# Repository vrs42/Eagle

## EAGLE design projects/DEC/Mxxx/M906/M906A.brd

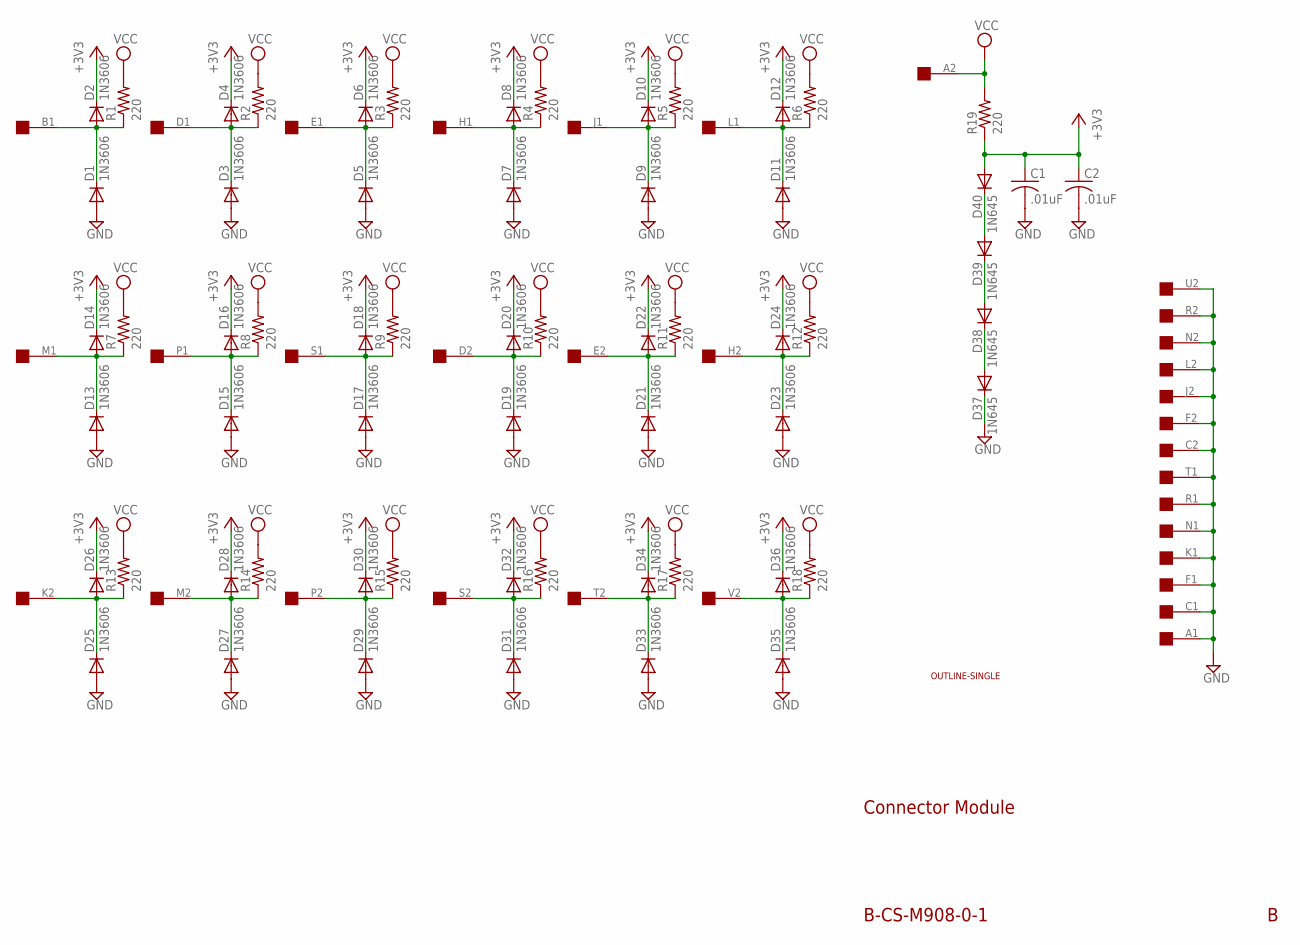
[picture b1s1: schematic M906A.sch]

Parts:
C1, C2: .01uF; C050-025X075
D1, D2, D3, D4, D5, D6, D7, D8, D9, D10, D11, D12, D13, D14, D15, D16, D17, D18, D19, D20, D21, D22, D23, D24, D25, D26, D27, D28, D29, D30, D31, D32, D33, D34, D35, D36: 1N3606; DO35-10
D37, D38, D39, D40: 1N645; DO35-10
R1, R2, R3, R4, R5, R6, R7, R8, R9, R10, R11, R12, R13, R14, R15, R16, R17, R18, R19: 220; 0207/10
U$1: SINGLE; EDGE-CON2
U$2: OUTLINE-SINGLE; SINGLE

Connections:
+3V3: C1.1, C2.1, D2.C, D4.C, D6.C, D8.C, D10.C, D12.C, D14.C, D16.C, D18.C, D20.C, D22.C, D24.C, D26.C, D28.C, D30.C, D32.C, D34.C, D36.C, D40.A, R19.1
GND: C1.2, C2.2, D1.A, D3.A, D5.A, D7.A, D9.A, D11.A, D13.A, D15.A, D17.A, D19.A, D21.A, D23.A, D25.A, D27.A, D29.A, D31.A, D33.A, D35.A, D37.C, U$1.A1, U$1.C1, U$1.C2, U$1.F1, U$1.F2, U$1.J2, U$1.K1, U$1.L2, U$1.N1, U$1.N2, U$1.R1, U$1.R2, U$1.T1, U$1.U2
unnamed: D1.C, D2.A, R1.1, U$1.B1
unnamed: D37.A, D38.C
unnamed: D38.A, D39.C
unnamed: D3.C, D4.A, R2.1, U$1.D1
unnamed: D39.A, D40.C
unnamed: D5.C, D6.A, R3.1, U$1.E1
unnamed: D7.C, D8.A, R4.1, U$1.H1
unnamed: D9.C, D10.A, R5.1, U$1.J1
unnamed: D11.C, D12.A, R6.1, U$1.L1
unnamed: D13.C, D14.A, R7.1, U$1.M1
unnamed: D15.C, D16.A, R8.1, U$1.P1
unnamed: D17.C, D18.A, R9.1, U$1.S1
unnamed: D19.C, D20.A, R10.1, U$1.D2
unnamed: D21.C, D22.A, R11.1, U$1.E2
unnamed: D23.C, D24.A, R12.1, U$1.H2
unnamed: D25.C, D26.A, R13.1, U$1.K2
unnamed: D27.C, D28.A, R14.1, U$1.M2
unnamed: D29.C, D30.A, R15.1, U$1.P2
unnamed: D31.C, D32.A, R16.1, U$1.S2
unnamed: D33.C, D34.A, R17.1, U$1.T2
unnamed: D35.C, D36.A, R18.1, U$1.V2
VCC: R1.2, R2.2, R3.2, R4.2, R5.2, R6.2, R7.2, R8.2, R9.2, R10.2, R11.2, R12.2, R13.2, R14.2, R15.2, R16.2, R17.2, R18.2, R19.2, U$1.A2

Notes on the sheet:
Connector Module
B-CS-M908-0-1

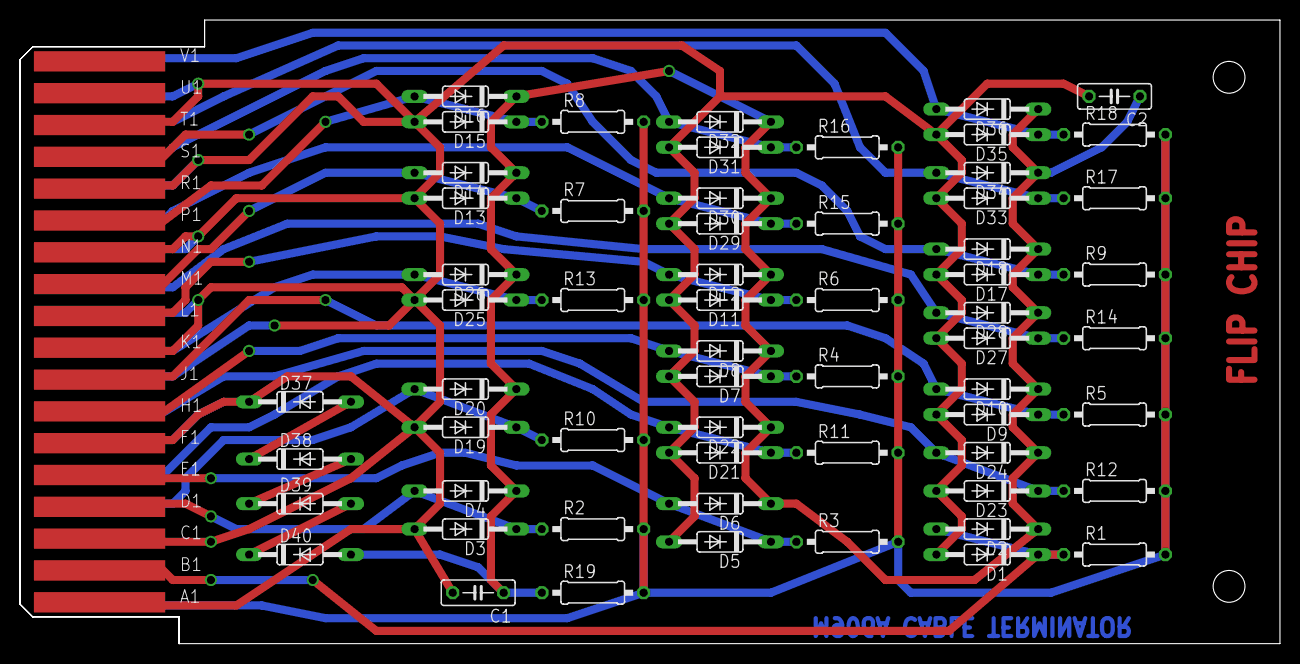
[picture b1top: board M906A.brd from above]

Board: 2 copper layers, 125.7 x 62.2 mm, 64 parts (0 on the bottom side), 24 nets.

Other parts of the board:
U$3: FLIPCHIP

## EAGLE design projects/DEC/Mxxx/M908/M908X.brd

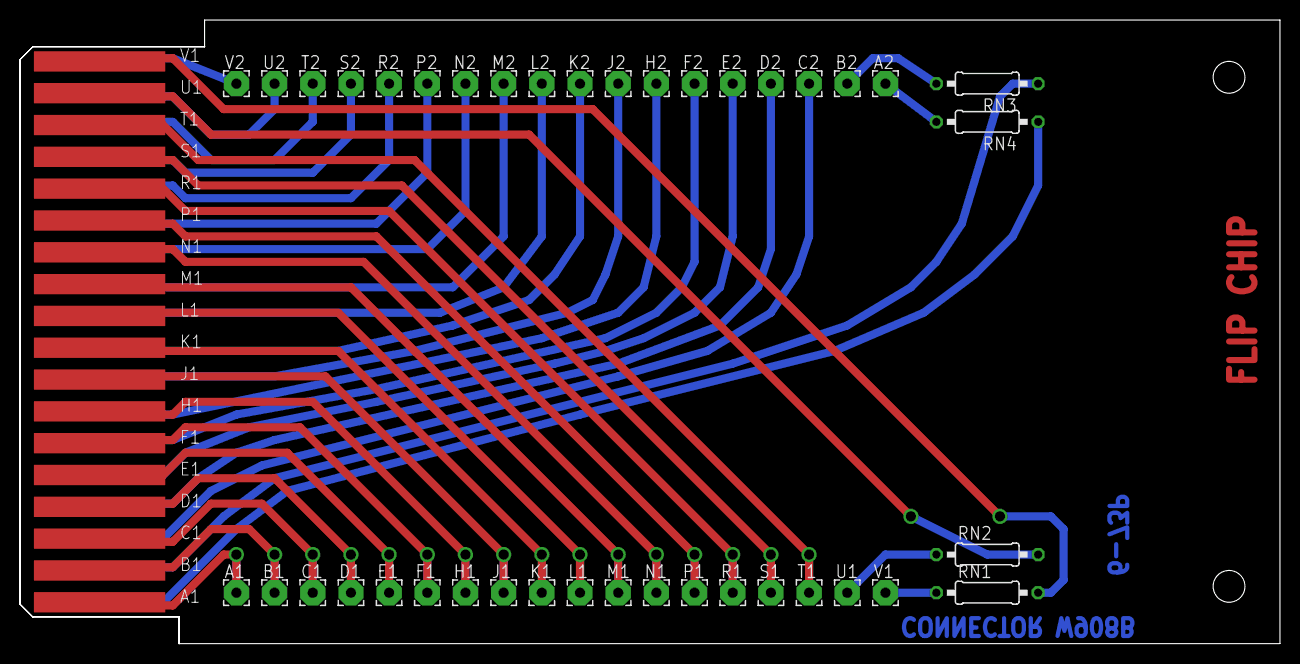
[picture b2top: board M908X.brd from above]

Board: 2 copper layers, 125.7 x 62.2 mm, 43 parts (0 on the bottom side), 40 nets.

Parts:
A1, A2: 2,54/1,0
B1, B2: 2,54/1,0
C1, C2: 2,54/1,0
D1, D2: 2,54/1,0
E1, E2: 2,54/1,0
F1, F2: 2,54/1,0
H1, H2: 2,54/1,0
J1, J2: 2,54/1,0
K1, K2: 2,54/1,0
L1, L2: 2,54/1,0
M1, M2: 2,54/1,0
N1, N2: 2,54/1,0
P1, P2: 2,54/1,0
R1, R2: 2,54/1,0
RN1, RN2, RN3, RN4: 10; 0207/10
S1, S2: 2,54/1,0
T1, T2: 2,54/1,0
U1, U2: 2,54/1,0
U$1: EDGE-CON2
U$2: OUTLINE-SINGLE; SINGLE
U$3: FLIPCHIP
V1, V2: 2,54/1,0

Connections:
unnamed: D1.1, U$1.D1
unnamed: E1.1, U$1.E1
unnamed: F1.1, U$1.F1
unnamed: H1.1, U$1.H1
unnamed: J1.1, U$1.J1
unnamed: K1.1, U$1.K1
unnamed: L1.1, U$1.L1
unnamed: M1.1, U$1.M1
unnamed: N1.1, U$1.N1
unnamed: P1.1, U$1.P1
unnamed: R1.1, U$1.R1
unnamed: S1.1, U$1.S1
unnamed: T1.1, U$1.T1
unnamed: RN2.2, U$1.U1
unnamed: RN1.2, U$1.V1
unnamed: A2.1, RN4.2
unnamed: B2.1, RN3.2
unnamed: C2.1, U$1.C2
unnamed: D2.1, U$1.D2
unnamed: E2.1, U$1.E2
unnamed: F2.1, U$1.F2
unnamed: H2.1, U$1.H2
unnamed: J2.1, U$1.J2
unnamed: K2.1, U$1.K2
unnamed: L2.1, U$1.L2
unnamed: M2.1, U$1.M2
unnamed: N2.1, U$1.N2
unnamed: P2.1, U$1.P2
unnamed: R2.1, U$1.R2
unnamed: S2.1, U$1.S2
unnamed: T2.1, U$1.T2
unnamed: U2.1, U$1.U2
unnamed: U$1.V2, V2.1
unnamed: RN1.1, V1.1
unnamed: RN2.1, U1.1
unnamed: RN3.1, U$1.B2
unnamed: RN4.1, U$1.A2
unnamed: A1.1, U$1.A1
unnamed: B1.1, U$1.B1
unnamed: C1.1, U$1.C1

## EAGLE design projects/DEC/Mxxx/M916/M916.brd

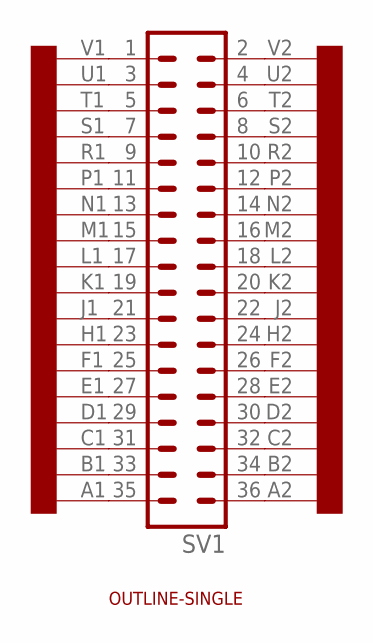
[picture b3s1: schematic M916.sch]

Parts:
SV1: MA18-2
U$1: EDGE-2CONNECTOR; EDGE-CON2
U$2: OUTLINE-SINGLE; SINGLE

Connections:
unnamed: SV1.1, U$1.V1
unnamed: SV1.3, U$1.U1
unnamed: SV1.5, U$1.T1
unnamed: SV1.7, U$1.S1
unnamed: SV1.9, U$1.R1
unnamed: SV1.11, U$1.P1
unnamed: SV1.13, U$1.N1
unnamed: SV1.15, U$1.M1
unnamed: SV1.17, U$1.L1
unnamed: SV1.19, U$1.K1
unnamed: SV1.21, U$1.J1
unnamed: SV1.23, U$1.H1
unnamed: SV1.25, U$1.F1
unnamed: SV1.27, U$1.E1
unnamed: SV1.29, U$1.D1
unnamed: SV1.31, U$1.C1
unnamed: SV1.33, U$1.B1
unnamed: SV1.35, U$1.A1
unnamed: SV1.2, U$1.V2
unnamed: SV1.4, U$1.U2
unnamed: SV1.6, U$1.T2
unnamed: SV1.8, U$1.S2
unnamed: SV1.10, U$1.R2
unnamed: SV1.12, U$1.P2
unnamed: SV1.14, U$1.N2
unnamed: SV1.16, U$1.M2
unnamed: SV1.18, U$1.L2
unnamed: SV1.20, U$1.K2
unnamed: SV1.22, U$1.J2
unnamed: SV1.24, U$1.H2
unnamed: SV1.26, U$1.F2
unnamed: SV1.28, U$1.E2
unnamed: SV1.30, U$1.D2
unnamed: SV1.32, U$1.C2
unnamed: SV1.34, U$1.B2
unnamed: SV1.36, U$1.A2

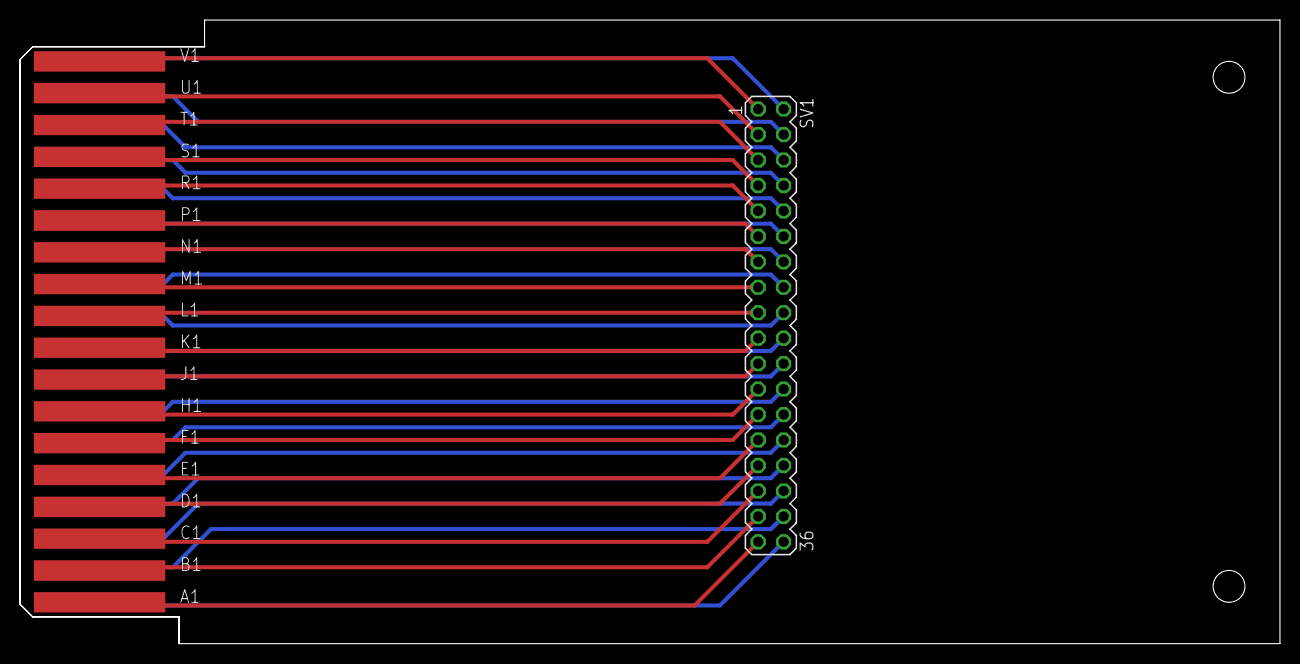
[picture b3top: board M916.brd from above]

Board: 2 copper layers, 125.7 x 62.2 mm, 3 parts (0 on the bottom side), 36 nets.

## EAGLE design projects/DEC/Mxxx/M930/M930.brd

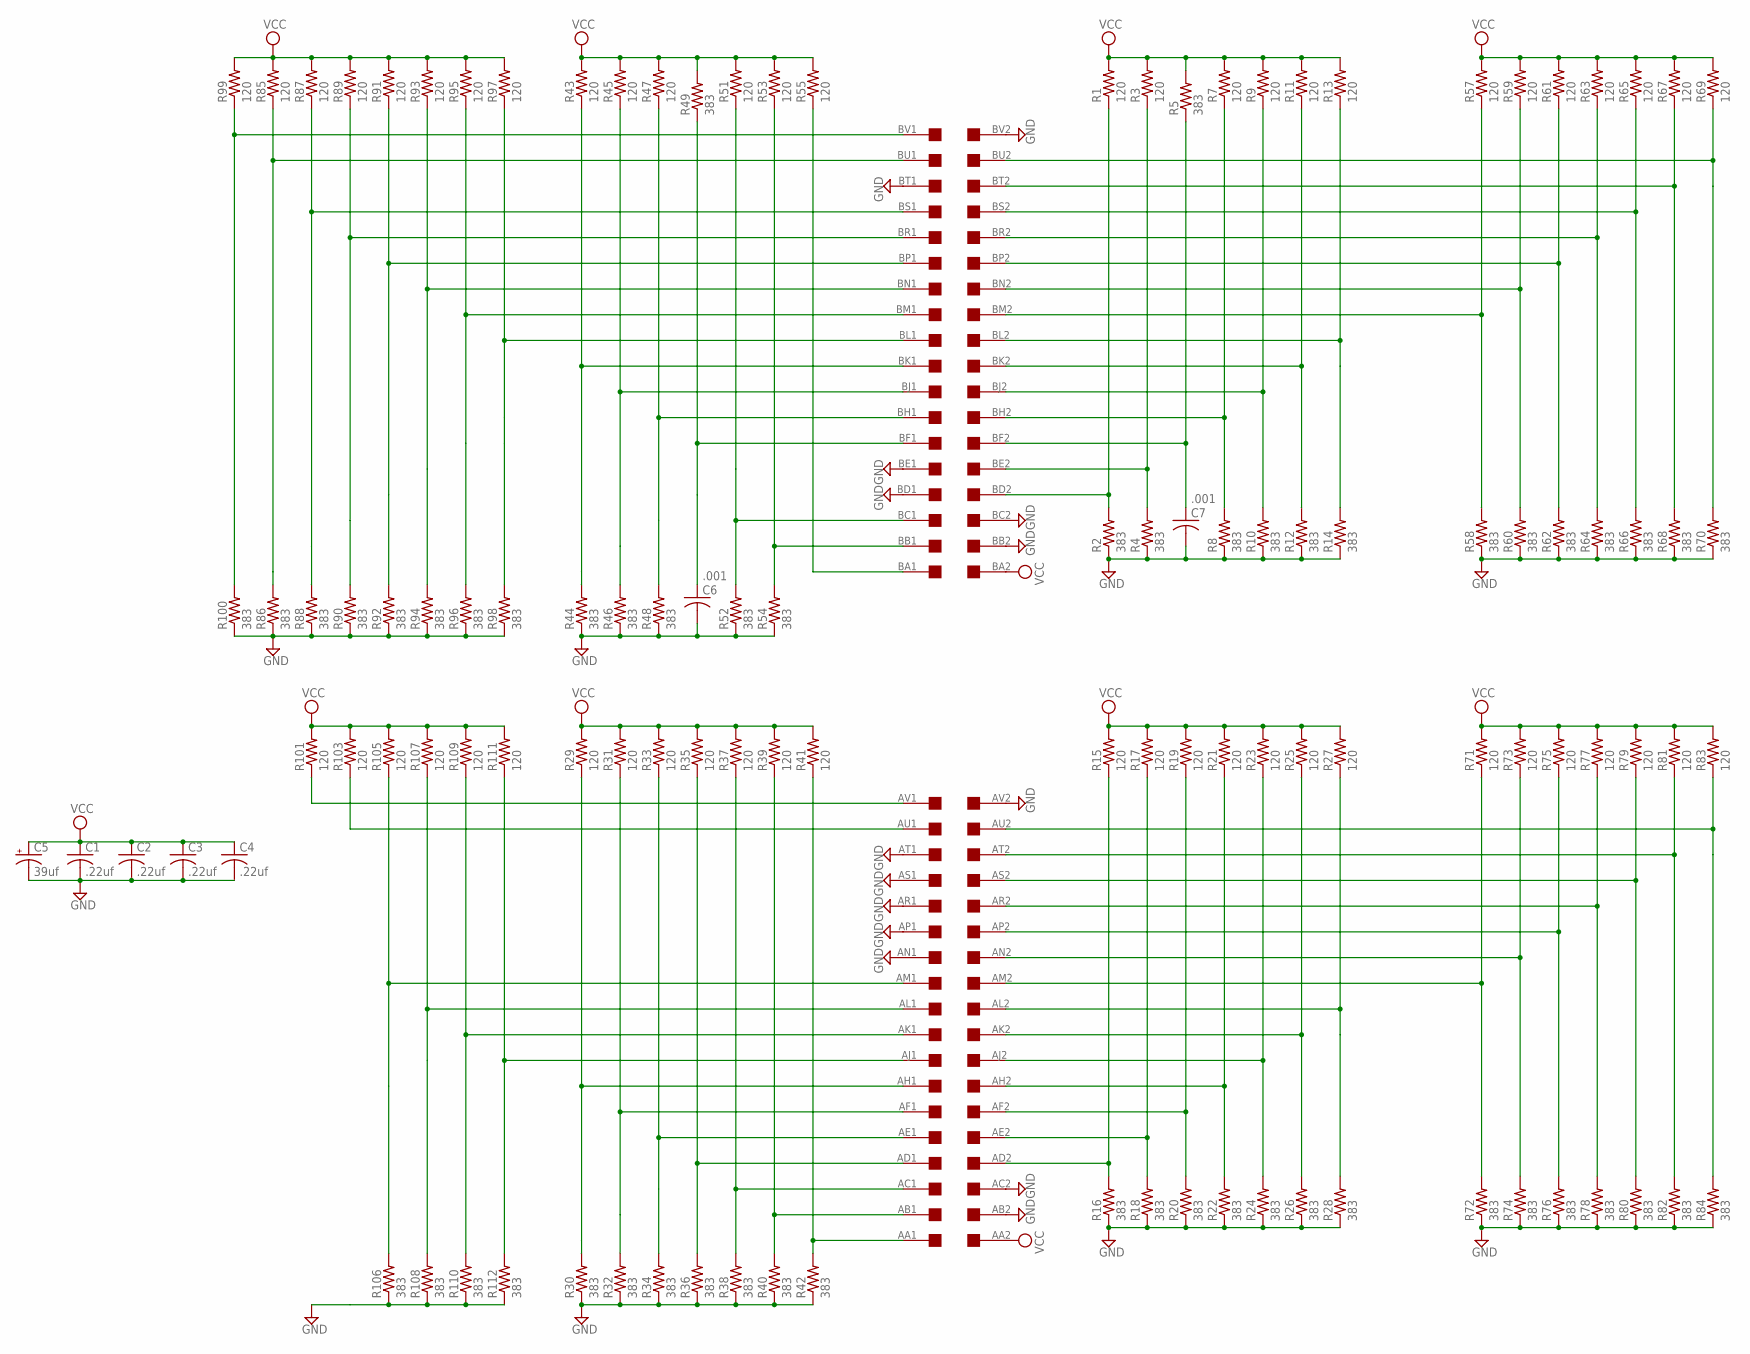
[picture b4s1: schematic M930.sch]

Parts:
C1, C2, C3, C4: .22uf; C050-025X075
C5: 39uf; E15-5
C6, C7: .001; C050-025X075
R1, R3, R7, R9, R11, R13, R15, R17, R19, R21, R23, R25, R27, R29, R31, R33, R35, R37, R39, R41, R43, R45, R47, R51, R53, R55, R57, R59, R61, R63, R65, R67, R69, R71, R73, R75, R77, R79, R81, R83, R85, R87, R89, R91, R93, R95, R97, R99, R101, R103, R105, R107, R109, R111: 120; 0207/10
R2, R4, R5, R8, R10, R12, R14, R16, R18, R20, R22, R24, R26, R28, R30, R32, R34, R36, R38, R40, R42, R44, R46, R48, R49, R52, R54, R58, R60, R62, R64, R66, R68, R70, R72, R74, R76, R78, R80, R82, R84, R86, R88, R90, R92, R94, R96, R98, R100, R106, R108, R110, R112: 383; 0207/10
U$1: DOUBLE; EDGE-CON4

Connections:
AA1: R41.1, R42.2, U$1.AA1
AB1: R39.1, R40.2, U$1.AB1
AC1: R37.1, R38.2, U$1.AC1
AD1: R35.1, R36.2, U$1.AD1
AD2: R15.1, R16.2, U$1.AD2
AE1: R33.1, R34.2, U$1.AE1
AE2: R17.1, R18.2, U$1.AE2
AF1: R31.1, R32.2, U$1.AF1
AF2: R19.1, R20.2, U$1.AF2
AH1: R29.1, R30.2, U$1.AH1
AH2: R21.1, R22.2, U$1.AH2
AJ1: R111.1, R112.2, U$1.AJ1
AJ2: R23.1, R24.2, U$1.AJ2
AK1: R109.1, R110.2, U$1.AK1
AK2: R25.1, R26.2, U$1.AK2
AL1: R107.1, R108.2, U$1.AL1
AL2: R27.1, R28.2, U$1.AL2
AM1: R105.1, R106.2, U$1.AM1
AM2: R71.1, R72.2, U$1.AM2
AN2: R73.1, R74.2, U$1.AN2
AP2: R75.1, R76.2, U$1.AP2
AR2: R77.1, R78.2, U$1.AR2
AS2: R79.1, R80.2, U$1.AS2
AT2: R81.1, R82.2, U$1.AT2
AU1: R103.1, U$1.AU1
AU2: R83.1, R84.2, U$1.AU2
AV1: R101.1, U$1.AV1
BA1: R55.1, U$1.BA1
BB1: R53.1, R54.2, U$1.BB1
BC1: R51.1, R52.2, U$1.BC1
BD2: R1.1, R2.2, U$1.BD2
BE2: R3.1, R4.2, U$1.BE2
BF1: C6.1, R49.1, U$1.BF1
BF2: C7.1, R5.1, U$1.BF2
BH1: R47.1, R48.2, U$1.BH1
BH2: R7.1, R8.2, U$1.BH2
BJ1: R45.1, R46.2, U$1.BJ1
BJ2: R9.1, R10.2, U$1.BJ2
BK1: R43.1, R44.2, U$1.BK1
BK2: R11.1, R12.2, U$1.BK2
BL1: R97.1, R98.2, U$1.BL1
BL2: R13.1, R14.2, U$1.BL2
BM1: R95.1, R96.2, U$1.BM1
BM2: R57.1, R58.2, U$1.BM2
BN1: R93.1, R94.2, U$1.BN1
BN2: R59.1, R60.2, U$1.BN2
BP1: R91.1, R92.2, U$1.BP1
BP2: R61.1, R62.2, U$1.BP2
BR1: R89.1, R90.2, U$1.BR1
BR2: R63.1, R64.2, U$1.BR2
BS1: R87.1, R88.2, U$1.BS1
BS2: R65.1, R66.2, U$1.BS2
BT2: R67.1, R68.2, U$1.BT2
BU1: R85.1, R86.2, U$1.BU1
BU2: R69.1, R70.2, U$1.BU2
BV1: R99.1, R100.2, U$1.BV1
GND: C1.2, C2.2, C3.2, C4.2, C5.-, C6.2, C7.2, R2.1, R4.1, R8.1, R10.1, R12.1, R14.1, R16.1, R18.1, R20.1, R22.1, R24.1, R26.1, R28.1, R30.1, R32.1, R34.1, R36.1, R38.1, R40.1, R42.1, R44.1, R46.1, R48.1, R52.1, R54.1, R58.1, R60.1, R62.1, R64.1, R66.1, R68.1, R70.1, R72.1, R74.1, R76.1, R78.1, R80.1, R82.1, R84.1, R86.1, R88.1, R90.1, R92.1, R94.1, R96.1, R98.1, R100.1, R106.1, R108.1, R110.1, R112.1, U$1.AB2, U$1.AC2, U$1.AN1, U$1.AP1, U$1.AR1, U$1.AS1, U$1.AT1, U$1.AV2, U$1.BB2, U$1.BC2, U$1.BD1, U$1.BE1, U$1.BT1, U$1.BV2
VCC: C1.1, C2.1, C3.1, C4.1, C5.+, R1.2, R3.2, R5.2, R7.2, R9.2, R11.2, R13.2, R15.2, R17.2, R19.2, R21.2, R23.2, R25.2, R27.2, R29.2, R31.2, R33.2, R35.2, R37.2, R39.2, R41.2, R43.2, R45.2, R47.2, R49.2, R51.2, R53.2, R55.2, R57.2, R59.2, R61.2, R63.2, R65.2, R67.2, R69.2, R71.2, R73.2, R75.2, R77.2, R79.2, R81.2, R83.2, R85.2, R87.2, R89.2, R91.2, R93.2, R95.2, R97.2, R99.2, R101.2, R103.2, R105.2, R107.2, R109.2, R111.2, U$1.AA2, U$1.BA2

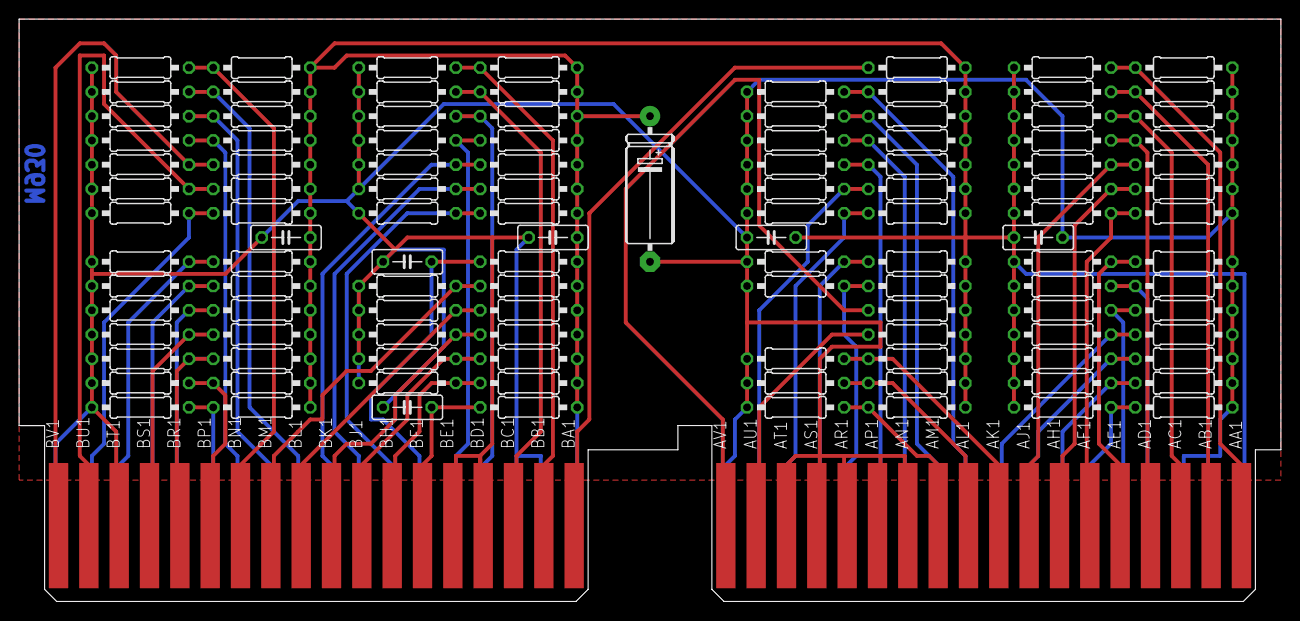
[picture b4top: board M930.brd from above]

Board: 2 copper layers, 132.1 x 61.0 mm, 115 parts (0 on the bottom side), 58 nets.
